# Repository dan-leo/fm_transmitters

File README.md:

# fm_transmitters
These fm transmitters work from 88 to 107.5 MHz. 

This was my first ever version.

<br>
<br>

Here I made it quite a bit more compact.

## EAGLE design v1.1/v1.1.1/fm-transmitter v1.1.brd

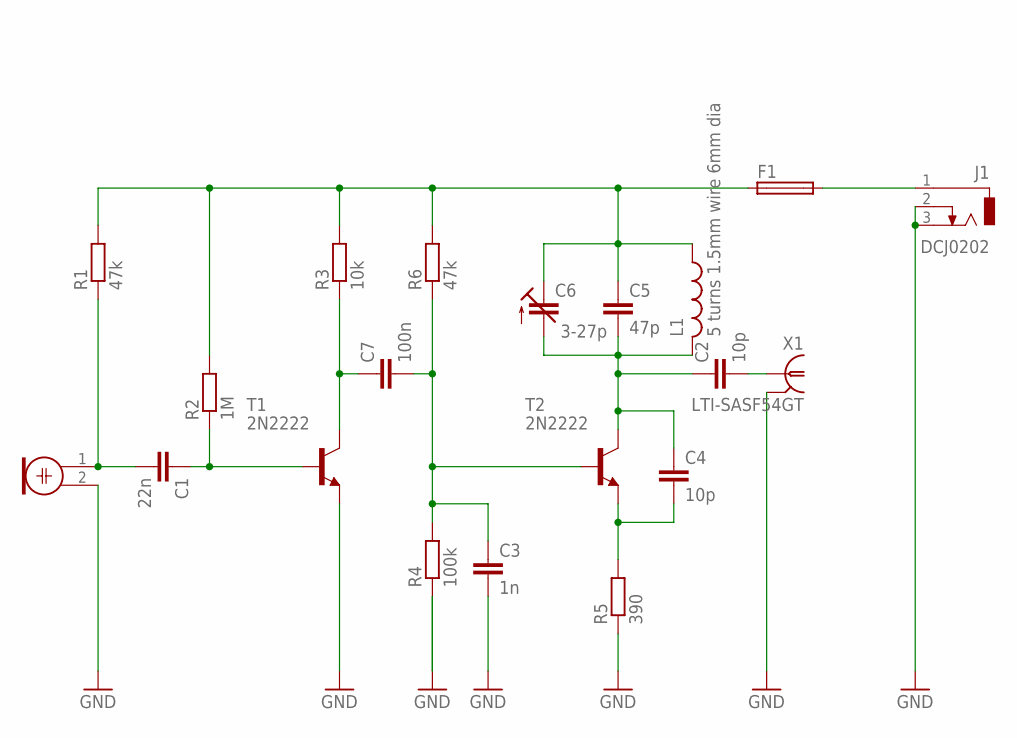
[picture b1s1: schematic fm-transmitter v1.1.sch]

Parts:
C1: 22n; C5B2.5
C2, C4: 10p; C5B2.5
C3: 1n; C5B2.5
C5: 47p; C5B2.5
C6: 3-27p; CTRIM3050.504
C7: 100n; C5B2.5
F1: TE5
J1: DCJ0202
L1: 5 turns 1.5mm wire 6mm dia; 0207/7
M1: ELECTRET_MICROPHON-F6050AP; F6050AP
R1, R6: 47k; 0207/10
R2: 1M; 0207/10
R3: 10k; 0207/10
R4: 100k; 0207/10
R5: 390; 0207/10
T1, T2: 2N2222; TO18
X1: LTI-SASF54GT

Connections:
GND: C3.2, J1.2, J1.3, M1.2, R4.1, R5.1, T1.1 (E), X1.2, X1.3 (2), X1.4 (2), X1.5 (2)
unnamed: C1.2, M1.1, R1.1
unnamed: C5.1, C6.1 (E), F1.1, L1.1, R1.2, R2.2, R3.2, R6.2
unnamed: C1.1, R2.1, T1.2 (B)
unnamed: C7.1, R3.1, T1.3 (C)
unnamed: C3.1, C7.2, R4.2, R6.1, T2.2 (B)
unnamed: C2.2, X1.1
unnamed: C2.1, C4.1, C5.2, C6.2 (A), L1.2, T2.3 (C)
unnamed: C4.2, R5.2, T2.1 (E)
unnamed: F1.2, J1.1

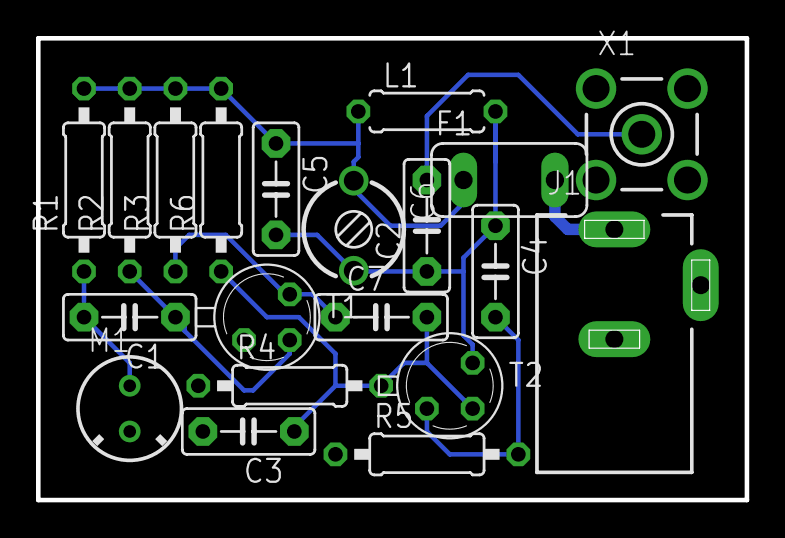
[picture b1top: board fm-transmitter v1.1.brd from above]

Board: 2 copper layers, 39.4 x 25.7 mm, 20 parts (0 on the bottom side), 10 nets.

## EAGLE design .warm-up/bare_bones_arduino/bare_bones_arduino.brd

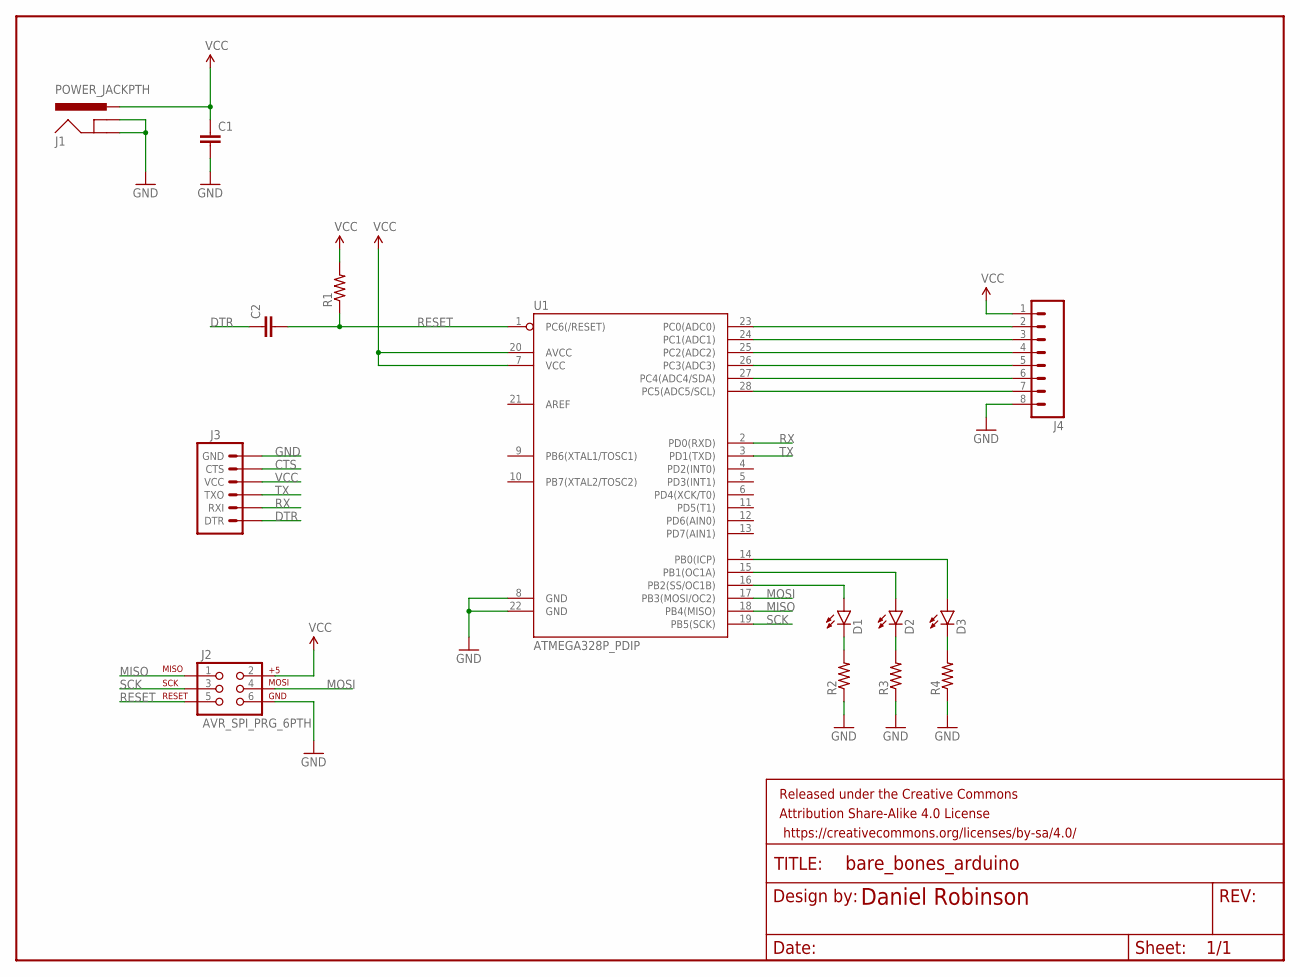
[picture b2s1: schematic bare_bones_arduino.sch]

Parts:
C1, C2: CAPPTH; CAP-PTH-SMALL
D1, D2, D3: LED5MM
FRAME1: FRAME-LETTER; CREATIVE_COMMONS
J1: POWER_JACKPTH; POWER_JACK_PTH
J2: AVR_SPI_PRG_6PTH; 2X3
J3: ARDUINO_SERIAL_PROGRAMPTH; 1X06
J4: M08SILK_FEMALE_PTH; 1X08
R1, R2, R3, R4: RESISTORPTH-1/4W; AXIAL-0.4
U1: ATMEGA328P_PDIP; DIL28-3

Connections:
CTS: J3.5 (CTS)
DTR: C2.1, J3.1 (DTR)
GND: C1.2, J1.GND, J1.GNDBREAK, J2.6, J3.6 (GND), J4.8, R2.P$1 (1), R3.P$1 (1), R4.P$1 (1), U1.8 (GND), U1.22 (GND)
MISO: J2.1, U1.18 (PB4(MISO))
MOSI: J2.4, U1.17 (PB3(MOSI/OC2))
unnamed: J4.2, U1.23 (PC0(ADC0))
unnamed: J4.5, U1.26 (PC3(ADC3))
unnamed: J4.6, U1.27 (PC4(ADC4/SDA))
unnamed: J4.3, U1.24 (PC1(ADC1))
unnamed: J4.4, U1.25 (PC2(ADC2))
unnamed: J4.7, U1.28 (PC5(ADC5/SCL))
unnamed: D1.A, U1.16 (PB2(SS/OC1B))
unnamed: D1.K (C), R2.P$2 (2)
unnamed: D2.K (C), R3.P$2 (2)
unnamed: D2.A, U1.15 (PB1(OC1A))
unnamed: D3.A, U1.14 (PB0(ICP))
unnamed: D3.K (C), R4.P$2 (2)
RESET: C2.2, J2.5, R1.P$1 (1), U1.1 (PC6(/RESET))
RX: J3.2 (RXI), U1.2 (PD0(RXD))
SCK: J2.3, U1.19 (PB5(SCK))
TX: J3.3 (TXO), U1.3 (PD1(TXD))
VCC: C1.1, J1.PWR, J2.2, J3.4 (VCC), J4.1, R1.P$2 (2), U1.7 (VCC), U1.20 (AVCC)

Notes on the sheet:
Daniel Robinson

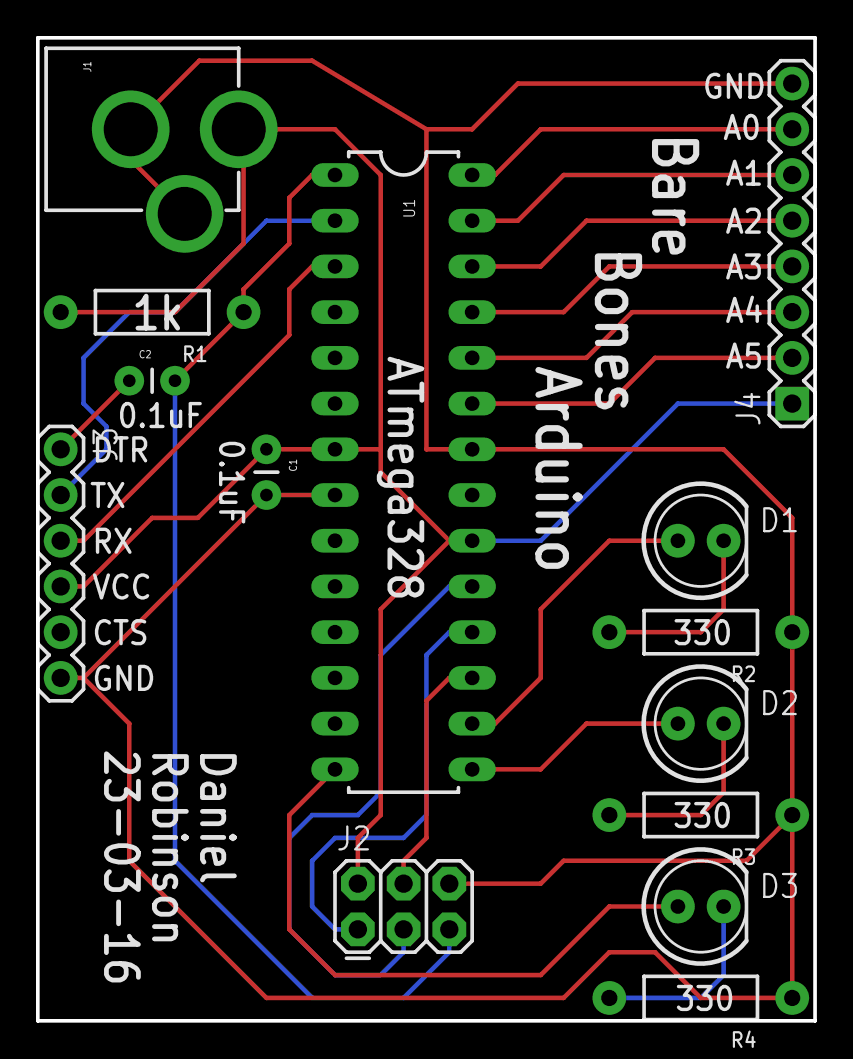
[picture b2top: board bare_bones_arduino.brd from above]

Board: 2 copper layers, 43.2 x 54.6 mm, 15 parts (0 on the bottom side), 21 nets.

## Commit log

2016-03-22 version 1.0 added
2016-03-23 warm-up tutorial complete
2016-03-23 added pic of v1.0
2016-03-23 v1.1 fm-transmitter added
2016-03-23 fuse added. transparencies added.
2016-03-28 added A4 print
2016-03-28 added gerbers

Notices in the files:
parts and their libraries:
SparkFun-Aesthetics: Licensing: Creative Commons ShareAlike 4.0 International - https://creativecommons.org/licenses/by-sa/4.0
SparkFun-Aesthetics: Released under the Creative Commons Attribution Share-Alike 4.0 License
SparkFun-Aesthetics: https://creativecommons.org/licenses/by-sa/4.0
